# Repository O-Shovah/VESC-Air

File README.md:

# VESC-Air

Variant of the VESC 6 ESC by Benjamin Vedder designed for small RC aircraft by Jens Schmelkus.

VESC Hardware is licensed under the Creative Commons Attribution-ShareAlike 4.0 International License. To view a copy of this license, visit http://creativecommons.org/licenses/by-sa/4.0/.

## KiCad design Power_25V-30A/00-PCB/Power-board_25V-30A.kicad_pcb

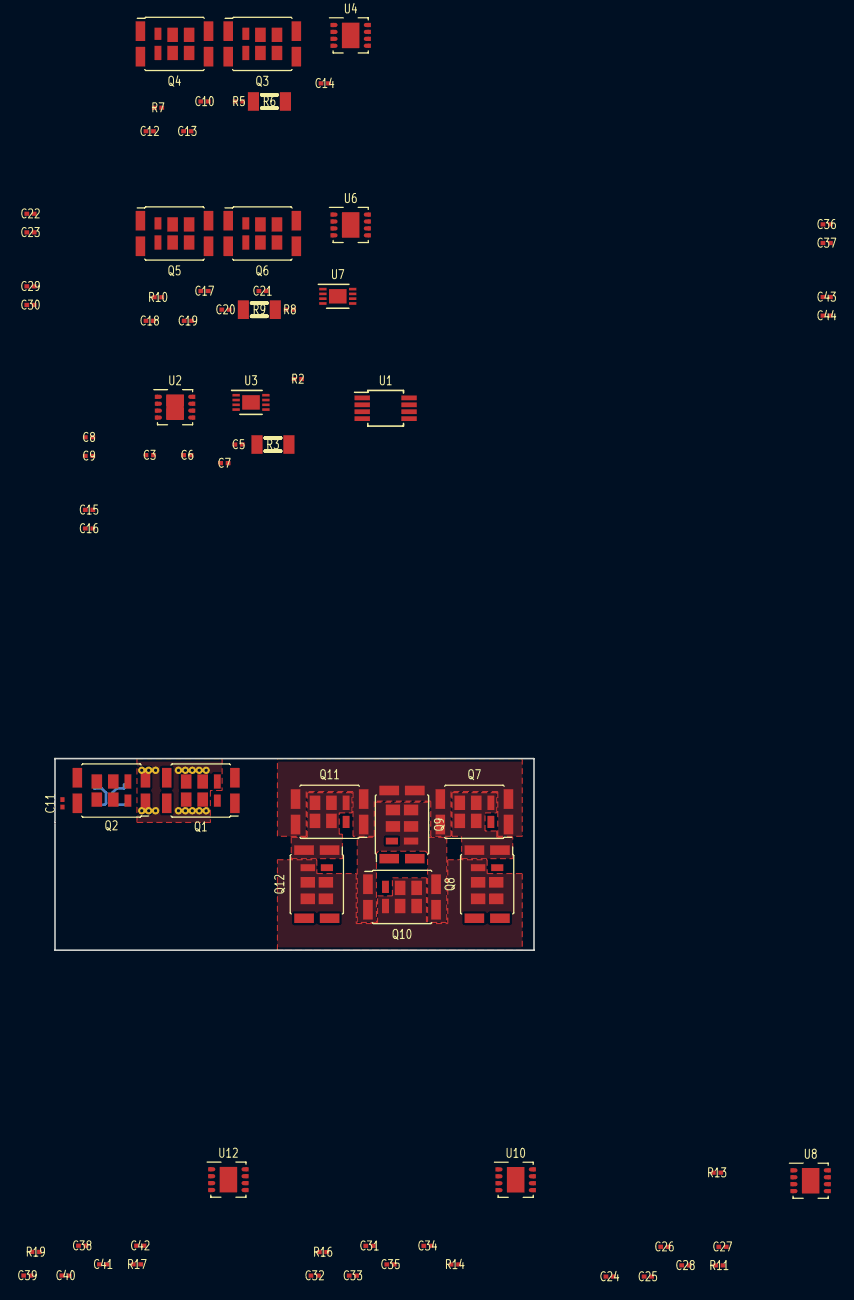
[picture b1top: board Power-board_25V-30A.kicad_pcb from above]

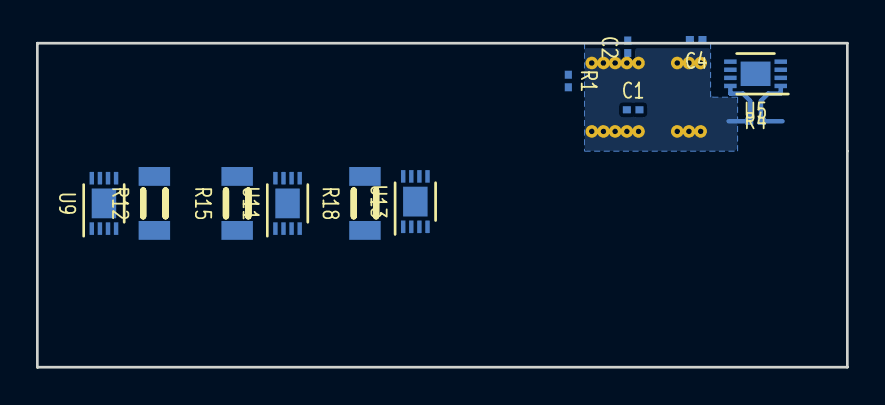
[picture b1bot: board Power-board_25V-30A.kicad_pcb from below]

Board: 2 copper layers, 45.0 x 18.0 mm, 88 parts (12 on the bottom side), 48 nets.

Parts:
C1, C4, C5, C11, C12, C18, C19, C25, C26, C32, C33, C39, C40: 4nF7; CAPC0603X33
C2, C3, C10, C17, C24, C31, C38: 2µF2; CAPC0603X33
C6, C7, C13, C14, C20, C21, C27, C28, C34, C35, C41, C42: 680µF_50V; CAPC0603X33
C8, C9, C15, C16, C22, C23, C29, C30, C36, C37, C43, C44: 0µF1; CAPC0603X33
Q1, Q2, Q3, Q4, Q5, Q6, Q7, Q8, Q9, Q10, Q11, Q12: IRL7486; DirectFET_ME
R1: 100R; RESC0603X30
R2, R4, R5, R7, R8, R10, R11, R13, R14, R16, R17, R19: 4R7; RESC0603X30
R3, R6, R9, R12, R15, R18: 0R0005; RESC3216X63
U1: AD8418; MSOP-8_3x3mm_P0.65mm
U2, U4, U6, U8, U10, U12: UCC27210; Texas_S-PVSON-N8
U3, U5, U7, U9, U11, U13: LT6118; DFN-8-1EP_3x2mm_P0.45mm

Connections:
+VDC: C4.1, C5.1, C6.1, C7.1, C11.1, C12.1, C13.1, C14.1, C18.1, C19.1, C20.1, C21.1, C25.1, C26.1, C27.1, C28.1, C32.1, C33.1, C34.1, C35.1, C39.1, C40.1, C41.1, C42.1, Q1.1, Q3.1, Q5.1, Q7.1, Q9.1, Q11.1
/Phase_U/Phase_Current_Out: R3.1, U3.1
/Phase_U/Voltage_Sens_High: C8.2, Q1.3, Q2.1, R3.2, U2.4, U3.8
/Phase_V/Phase_Current_Out: R6.1, U5.1
/Phase_V/Voltage_Sens_High: C15.2, Q3.3, Q4.1, R6.2, U4.4, U5.8
/Phase_W/Phase_Current_Out: R9.1, U7.1
/Phase_W/Voltage_Sens_High: C22.2, Q5.3, Q6.1, R9.2, U6.4, U7.8
/Phase_X/Phase_Current_Out: R12.1, U9.1
/Phase_X/Voltage_Sens_High: C29.2, Q7.3, Q8.1, R12.2, U8.4, U9.8
/Phase_Y/Phase_Current_Out: R18.1, U13.1
/Phase_Y/Voltage_Sens_High: C43.2, Q11.3, Q12.1, R18.2, U12.4, U13.8
/Phase_Z/Phase_Current_Out: R15.1, U11.1
/Phase_Z/Voltage_Sens_High: C36.2, Q9.3, Q10.1, R15.2, U10.4, U11.8
GND: C1.2, C2.2, C3.2, C4.2, C5.2, C6.2, C7.2, C9.2, C10.2, C11.2, C12.2, C13.2, C14.2, C16.2, C17.2, C18.2, C19.2, C20.2, C21.2, C23.2, C24.2, C25.2, C26.2, C27.2, C28.2, C30.2, C31.2, C32.2, C33.2, C34.2, C35.2, C37.2, C38.2, C39.2, C40.2, C41.2, C42.2, C44.2, Q2.3, Q4.3, Q6.3, Q8.3, Q10.3, Q12.3, U1.2, U1.3, U2.7, U2.9, U3.2, U3.4, U3.5, U3.9, U4.7, U4.9, U5.2, U5.4, U5.5, U5.9, U6.7, U6.9, U7.2, U7.4, U7.5, U7.9, U8.7, U8.9, U9.2, U9.4, U9.5, U9.9, U10.7, U10.9, U11.2, U11.4, U11.5, U11.9, U12.7, U12.9, U13.2, U13.4, U13.5, U13.9
unnamed: C1.1, R1.1
unnamed: C8.1, U2.2
unnamed: C15.1, U4.2
unnamed: C22.1, U6.2
unnamed: C29.1, U8.2
unnamed: C36.1, U10.2
unnamed: C43.1, U12.2
unnamed: Q1.2, R2.1
unnamed: Q2.2, R4.1
unnamed: Q3.2, R5.1
unnamed: Q4.2, R7.1
unnamed: Q5.2, R8.1
unnamed: Q6.2, R10.1
unnamed: Q7.2, R11.1
unnamed: Q8.2, R13.1
unnamed: Q9.2, R14.1
unnamed: Q10.2, R16.1
unnamed: Q11.2, R17.1
unnamed: Q12.2, R19.1
unnamed: R1.2, U1.5
unnamed: R2.2, U2.3
unnamed: R4.2, U2.8
unnamed: R5.2, U4.3
unnamed: R7.2, U4.8
unnamed: R8.2, U6.3
unnamed: R10.2, U6.8
unnamed: R11.2, U8.3
unnamed: R13.2, U8.8
unnamed: R14.2, U10.3
unnamed: R16.2, U10.8
unnamed: R17.2, U12.3
unnamed: R19.2, U12.8
VAA: C2.1, U1.6, U1.7
VCC: C3.1, C9.1, C10.1, C16.1, C17.1, C23.1, C24.1, C30.1, C31.1, C37.1, C38.1, C44.1, U2.1, U3.7, U4.1, U5.7, U6.1, U7.7, U8.1, U9.7, U10.1, U11.7, U12.1, U13.7

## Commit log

2017-11-22 added revision_00 branch
2017-11-23 sorted folder structure into controller board an power boards
2017-11-24 added schematic fpr 25 V power board
2017-11-25 Schematic concept Phase added
2017-11-26 Multiplied Phase Schematics
2017-11-26 Changed footprints, used new shunt footprints
2017-11-27 testing arrangements for 3 phase power stage
